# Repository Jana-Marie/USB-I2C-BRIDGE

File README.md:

# USB-I2C-BRIDGE

CP2112 based USB I2C bridge.

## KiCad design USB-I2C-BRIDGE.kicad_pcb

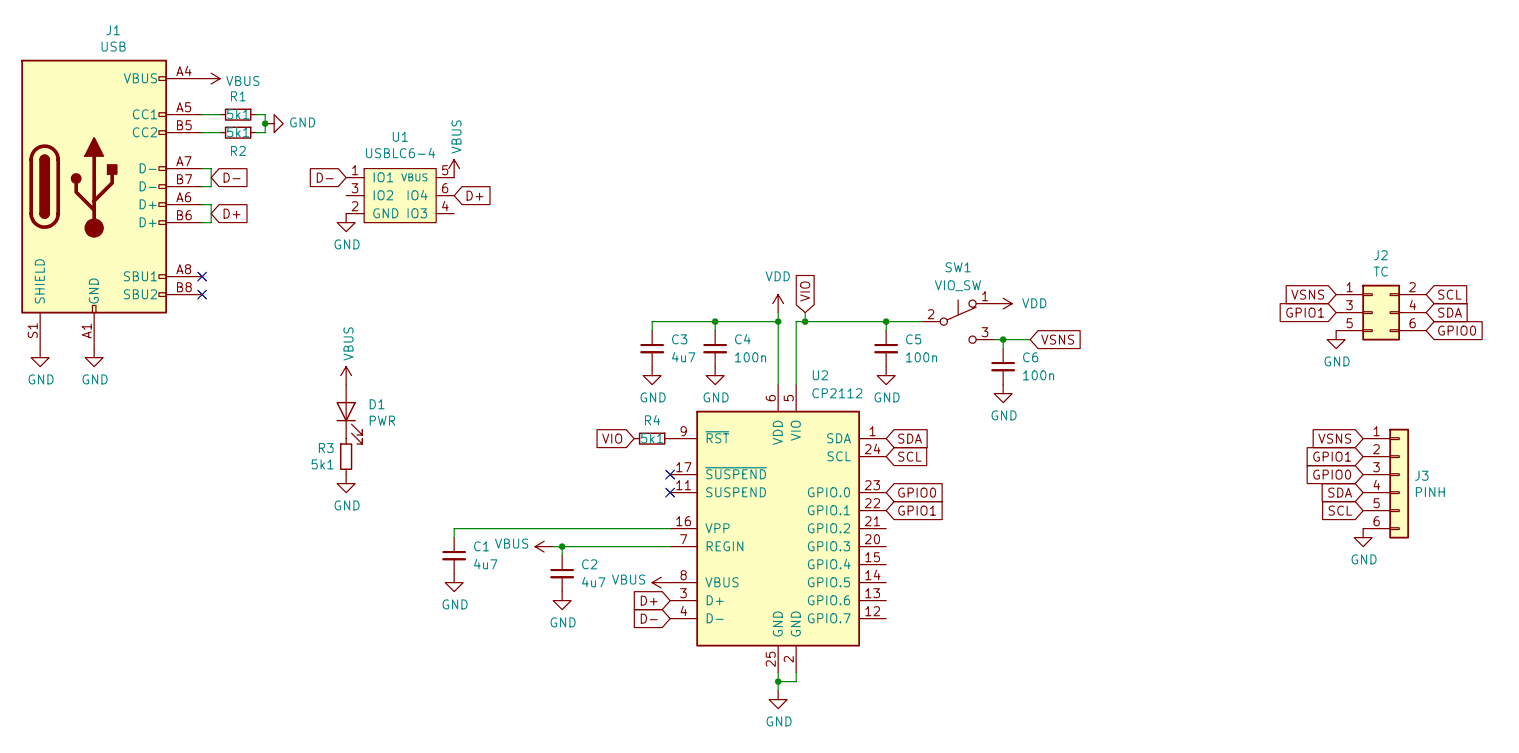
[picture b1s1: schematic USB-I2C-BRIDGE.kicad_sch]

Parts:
C1, C2, C3: 4u7; C_0805
C4, C5, C6: 100n; C_0402
D1: PWR; LED_0603_1608Metric
J1: USB; USB-C 16Pin
J2: TC; IDC-Header_2x03_P2.54mm_Vertical_center
J3: PINH; PinHeader_1x06_P2.54mm_Vertical_center
R1, R2, R3, R4: 5k1; R_0402
SW1: VIO_SW; SW_SPDT_PCM12
U1: USBLC6-4; SOT-23-6
U2: CP2112; QFN-24-1EP_4x4mm_P0.5mm_EP2.6x2.6mm

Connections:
D+: J1.A6 (D+), J1.B6 (D+), U1.6 (IO4), U2.3 (D+)
D-: J1.A7 (D-), J1.B7 (D-), U1.1 (IO1), U2.4 (D-)
GND: C1.2, C2.2, C3.2, C4.2, C5.2, C6.2, J1.A1 (GND), J1.A12 (GND), J1.B1 (GND), J1.B12 (GND), J1.S1 (SHIELD), J2.5, J3.6, R1.1, R2.1, R3.2, U1.2 (GND), U2.2 (GND), U2.25 (GND)
GPIO0: J2.6, J3.3, U2.23 (GPIO.0)
GPIO1: J2.3, J3.2, U2.22 (GPIO.1)
unnamed: C1.1, U2.16 (VPP)
unnamed: D1.1 (K), R3.1
unnamed: J1.A5 (CC1), R1.2
unnamed: J1.B5 (CC2), R2.2
unnamed: R4.1, U2.9 (~RST)
SCL: J2.2, J3.5, U2.24 (SCL)
SDA: J2.4, J3.4, U2.1 (SDA)
VBUS: C2.1, D1.2 (A), J1.A4 (VBUS), J1.A9 (VBUS), J1.B4 (VBUS), J1.B9 (VBUS), U1.5 (VBUS), U2.7 (REGIN), U2.8 (VBUS)
VDD: C3.1, C4.1, SW1.1 (A), U2.6 (VDD)
VIO: C5.1, R4.2, SW1.2 (B), U2.5 (VIO)
VSNS: C6.1, J2.1, J3.1, SW1.3 (C)

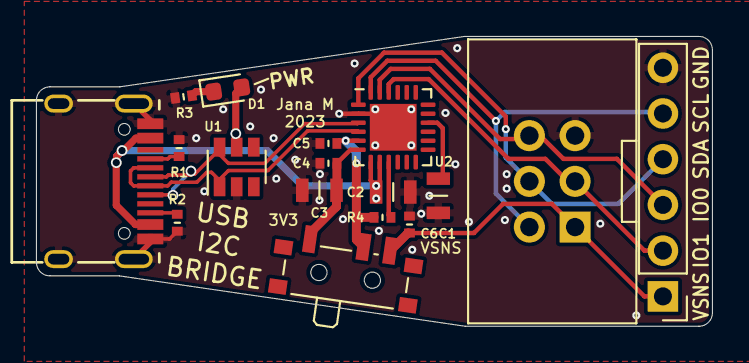
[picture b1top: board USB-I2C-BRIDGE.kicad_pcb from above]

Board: 2 copper layers, 37.6 x 16.1 mm, 17 parts (0 on the bottom side), 16 nets.

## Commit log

2023-01-01 added gitignore
2023-01-01 added project files
2023-01-01 added images and updated readme
2023-01-01 Create LICENSE
